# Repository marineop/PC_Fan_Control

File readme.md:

## Introduction
I have a PC fan that I removed from a CPU liquid cooler, and I'm powering it with a 12V power supply to use it for air filtration.  
However, when it's late at night, the fan's noise is a bit loud. But isn't this a PWM fan? I could use a development board to output a PWM signal and control the speed, but then I'd be short a development board.  
While searching online, I happened to come across a few useful online resources. I realized that in this day and age, this is actually possible to DIY a PCB board for simple device controls.  
* [Noctua PWM specifications white paper](https://cdn.noctua.at/media/Noctua_PWM_specifications_white_paper.pdf)
* [KiCad tutorial video from DigiKey](https://www.youtube.com/watch?v=vaCVh2SAZY4&list=PLEBQazB0HUyR24ckSZ5u05TZHV9khgA1O&index=1)
* [TI Power Dedigner](https://webench.ti.com/power-designer/)
* [OSH Park](https://oshpark.com/)
* [Mouser](https://www.mouser.com)

## Functionality

## Schematic - KiCad, Ti Power Deisgner  
* [KiCad](https://www.kicad.org/)  

## PCB Layout - KiCad  
* Front side

* Back side

### PCB Fabrication - OSH Park  

### Order Components - Mouser  

### Solder  

### Firmware  
* Programmer: STLINK-V3SET
* IDE: STM32CubeIDE
* Pin Define
    * PA7: PWM, TIM14_CH1
    * PA6: tachometer, TIM16_CH1
    * PB0: Rotary Encoder A (DI)
    * PB5: Rotary Encoder B (DI)
    * PA2: USART_TX
    * PA3: USART_RX
* Rotary Encoder Debouncing
    * Use TIM3 to periodically record last 10 pin states
        * if current state is 0, and there are at least eight 1s in the history, then change state to 1
        * if current state is 1, and there are at least eight 0s in the history, then change state to 0
* Debug USART: 115200, N, 8, 1

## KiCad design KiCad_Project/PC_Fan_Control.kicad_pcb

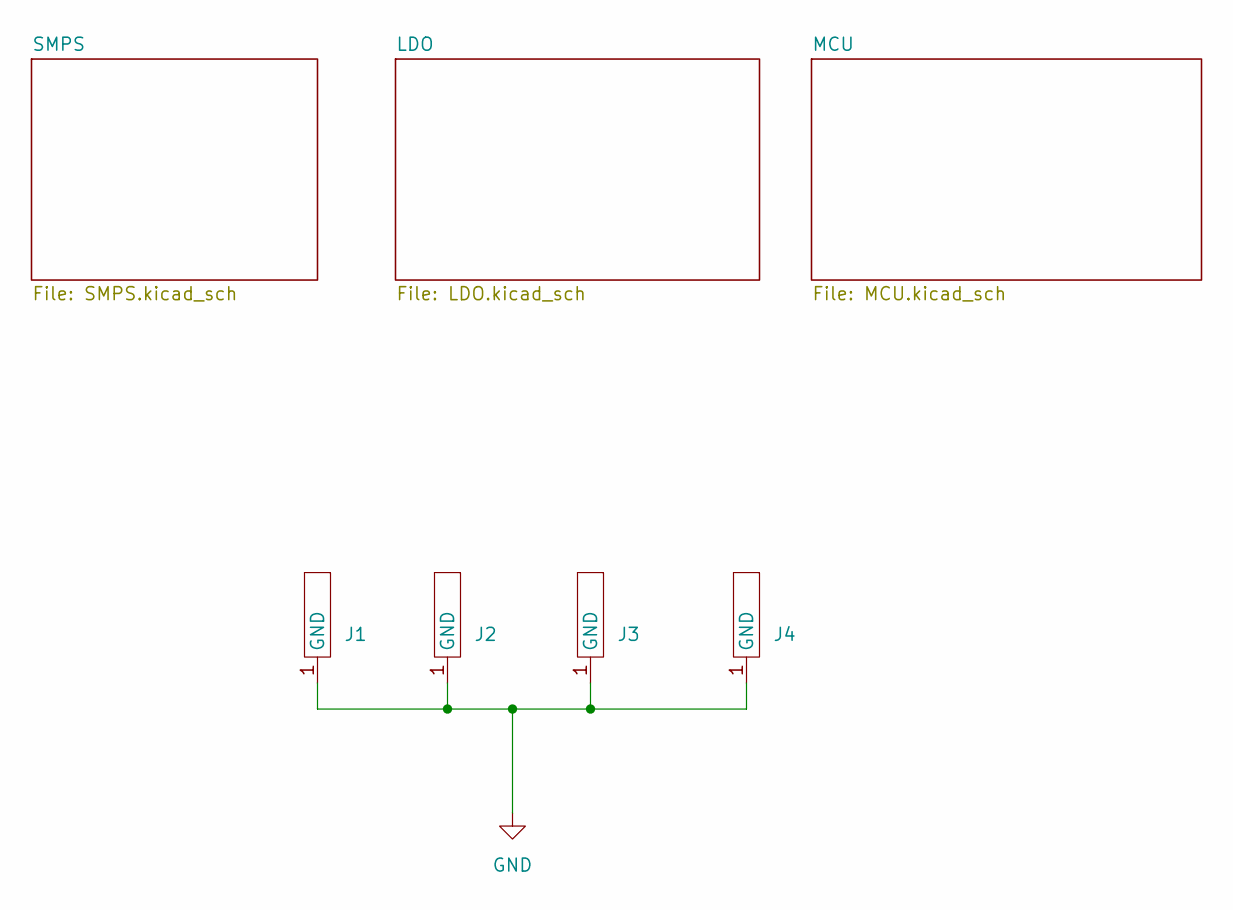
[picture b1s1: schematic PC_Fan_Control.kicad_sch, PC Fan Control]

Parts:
J1, J2, J3, J4: Standoff

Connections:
GND: J1.1 (GND), J2.1 (GND), J3.1 (GND), J4.1 (GND); also elsewhere on the board

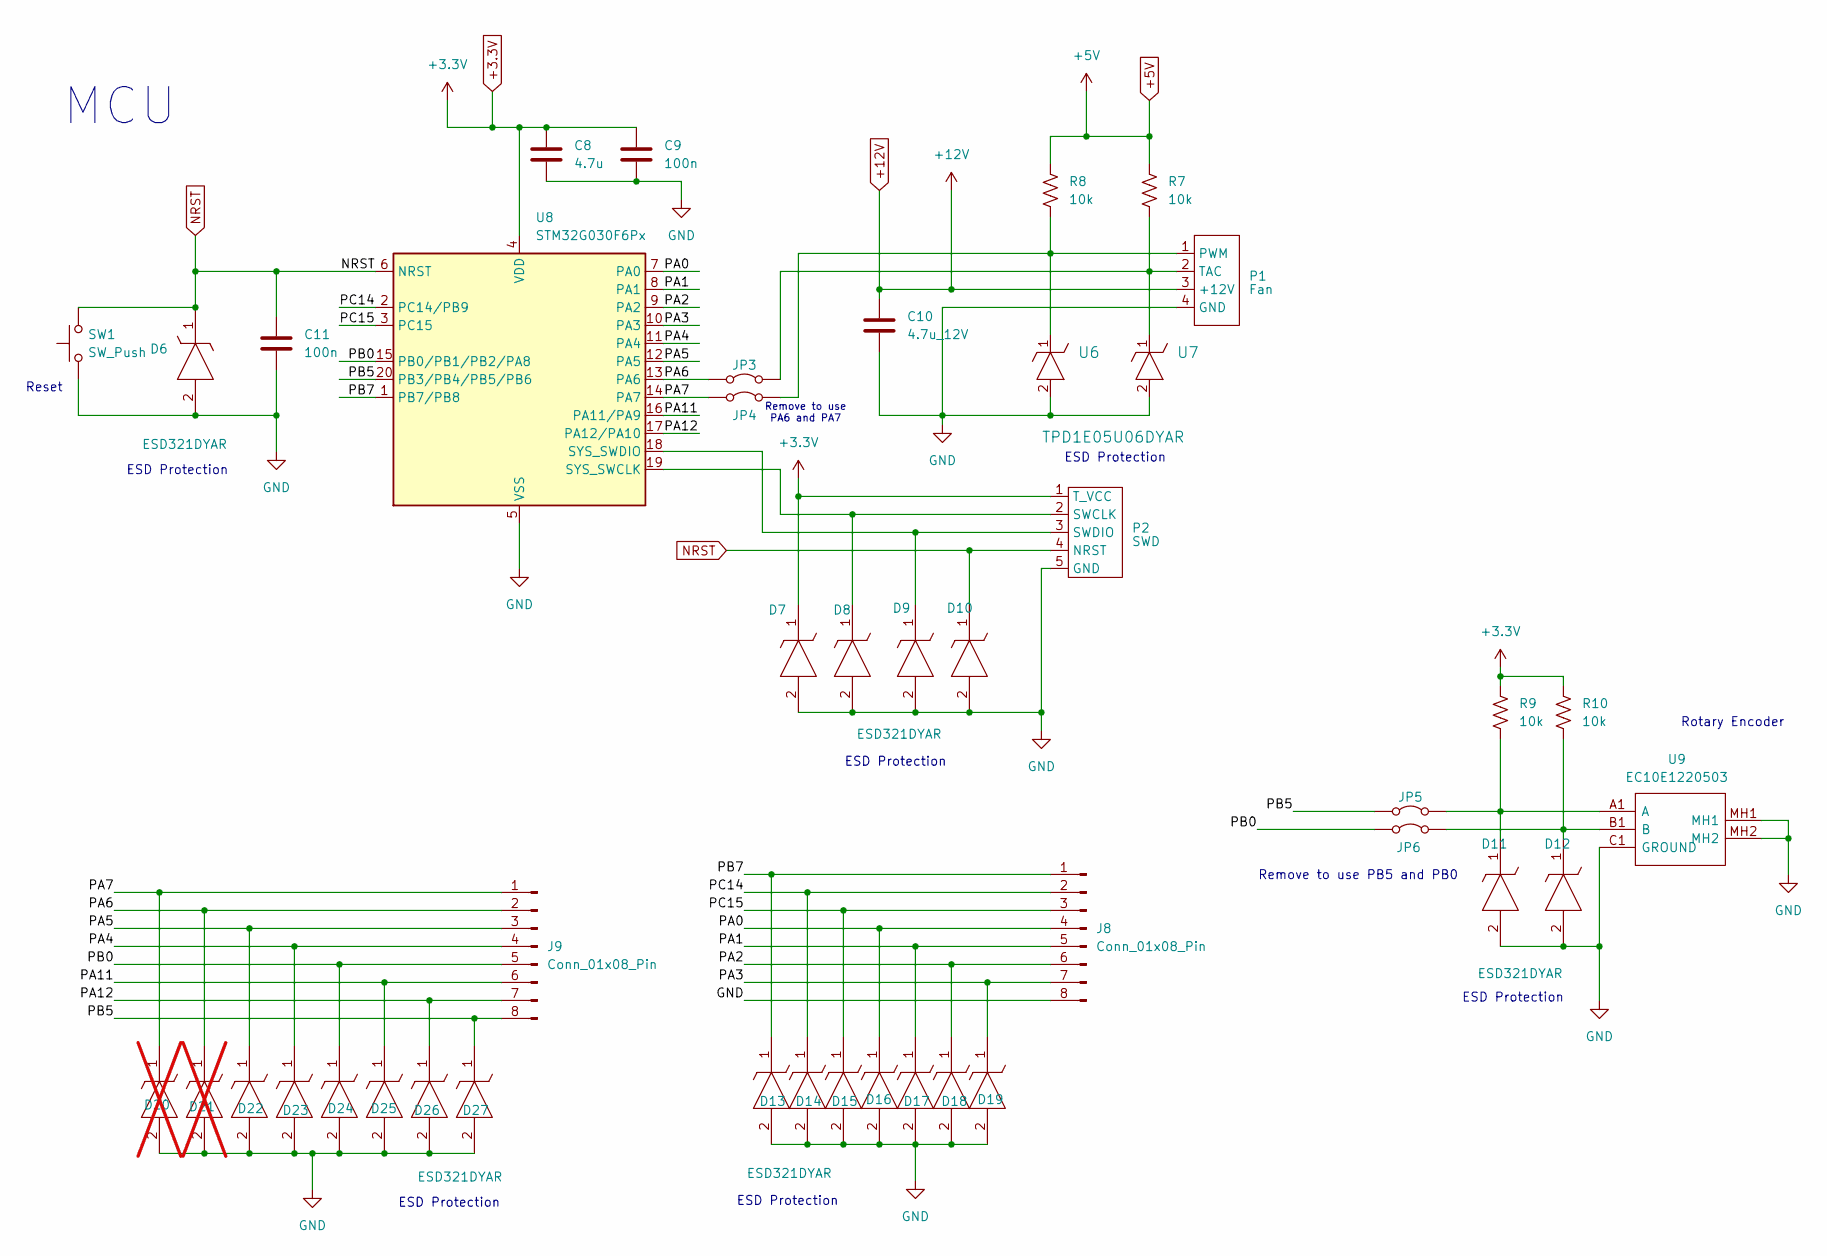
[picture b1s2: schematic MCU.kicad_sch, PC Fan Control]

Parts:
C8: 4.7u; C_0805_2012Metric_Pad1.18x1.45mm_HandSolder
C9, C11: 100n; C_0805_2012Metric_Pad1.18x1.45mm_HandSolder
C10: 4.7u_12V; C_0805_2012Metric_Pad1.18x1.45mm_HandSolder
D6, D7, D8, D9, D10, D11, D12, D13, D14, D15, D16, D17, D18, D19, D22, D23, D24, D25, D26, D27: ESD321DYAR; SOT (SOD-523)_Ti_DYA; Mouser Part Number 595-ESD321DYAR
D20, D21: ESD321DYAR; SOT (SOD-523)_Ti_DYA; Mouser Part Number 595-ESD321DYAR; not fitted
J8, J9: Conn_01x08_Pin; PinSocket_1x08_P2.54mm_Vertical
JP3, JP4, JP5, JP6: Jumper_2_Bridged; PinHeader_1x02_P2.54mm_Vertical
P1: Fan; PinHeader_1x04_P2.54mm_Horizontal
P2: SWD; PinHeader_1x05_P2.54mm_Vertical
R7, R8, R9, R10: 10k; R_0805_2012Metric_Pad1.20x1.40mm_HandSolder
SW1: SW_Push; SW_PUSH_6mm_H9.5mm
U6, U7: TPD1E05U06DYAR; SOT5x3_DYA_TEX
U8: STM32G030F6Px; TSSOP-20_4.4x6.5mm_P0.65mm
U9: EC10E1220503; Mouser Part Number 688-EC10E1220503

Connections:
+3.3V: C8.1, C9.1, D7.1, P2.1 (T_VCC), R9.1, R10.1, U8.4 (VDD); also elsewhere on the board
+5V: R7.1, R8.1; also elsewhere on the board
+12V: C10.1, P1.3 (+12V); also elsewhere on the board
/MCU/PA0: D16.1, J8.4, U8.7 (PA0)
/MCU/PA1: D17.1, J8.5, U8.8 (PA1)
/MCU/PA2: D18.1, J8.6, U8.9 (PA2)
/MCU/PA3: D19.1, J8.7, U8.10 (PA3)
/MCU/PA4: D23.1, J9.4, U8.11 (PA4)
/MCU/PA5: D22.1, J9.3, U8.12 (PA5)
/MCU/PA6: D21.1, J9.2, JP3.1 (A), U8.13 (PA6)
/MCU/PA7: D20.1, J9.1, JP4.1 (A), U8.14 (PA7)
/MCU/PA11: D25.1, J9.6, U8.16 (PA11/PA9)
/MCU/PA12: D26.1, J9.7, U8.17 (PA12/PA10)
/MCU/PB0: D24.1, J9.5, JP6.1 (A), U8.15 (PB0/PB1/PB2/PA8)
/MCU/PB5: D27.1, J9.8, JP5.1 (A), U8.20 (PB3/PB4/PB5/PB6)
/MCU/PB7: D13.1, J8.1, U8.1 (PB7/PB8)
/MCU/PC14: D14.1, J8.2, U8.2 (PC14/PB9)
/MCU/PC15: D15.1, J8.3, U8.3 (PC15)
GND: C8.2, C9.2, C10.2, C11.2, D6.2, D7.2, D8.2, D9.2, D10.2, D11.2, D12.2, D13.2, D14.2, D15.2, D16.2, D17.2, D18.2, D19.2, D20.2, D21.2, D22.2, D23.2, D24.2, D25.2, D26.2, D27.2, J8.8, P1.4 (GND), P2.5 (GND), SW1.1, U6.2, U7.2, U8.5 (VSS), U9.C1 (GROUND), U9.MH1, U9.MH2; also elsewhere on the board
NRST: C11.1, D6.1, D10.1, P2.4 (NRST), SW1.2, U8.6 (NRST)
unnamed: JP3.2 (B), P1.2 (TAC), R7.2, U7.1
unnamed: JP4.2 (B), P1.1 (PWM), R8.2, U6.1
unnamed: D11.1, JP5.2 (B), R9.2, U9.A1 (A)
unnamed: D12.1, JP6.2 (B), R10.2, U9.B1 (B)
unnamed: D8.1, P2.2 (SWCLK), U8.19 (SYS_SWCLK)
unnamed: D9.1, P2.3 (SWDIO), U8.18 (SYS_SWDIO)

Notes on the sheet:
ESD Protection
Remove to use PA6 and PA7
Rotary Encoder
MCU
Remove to use PB5 and PB0
Reset

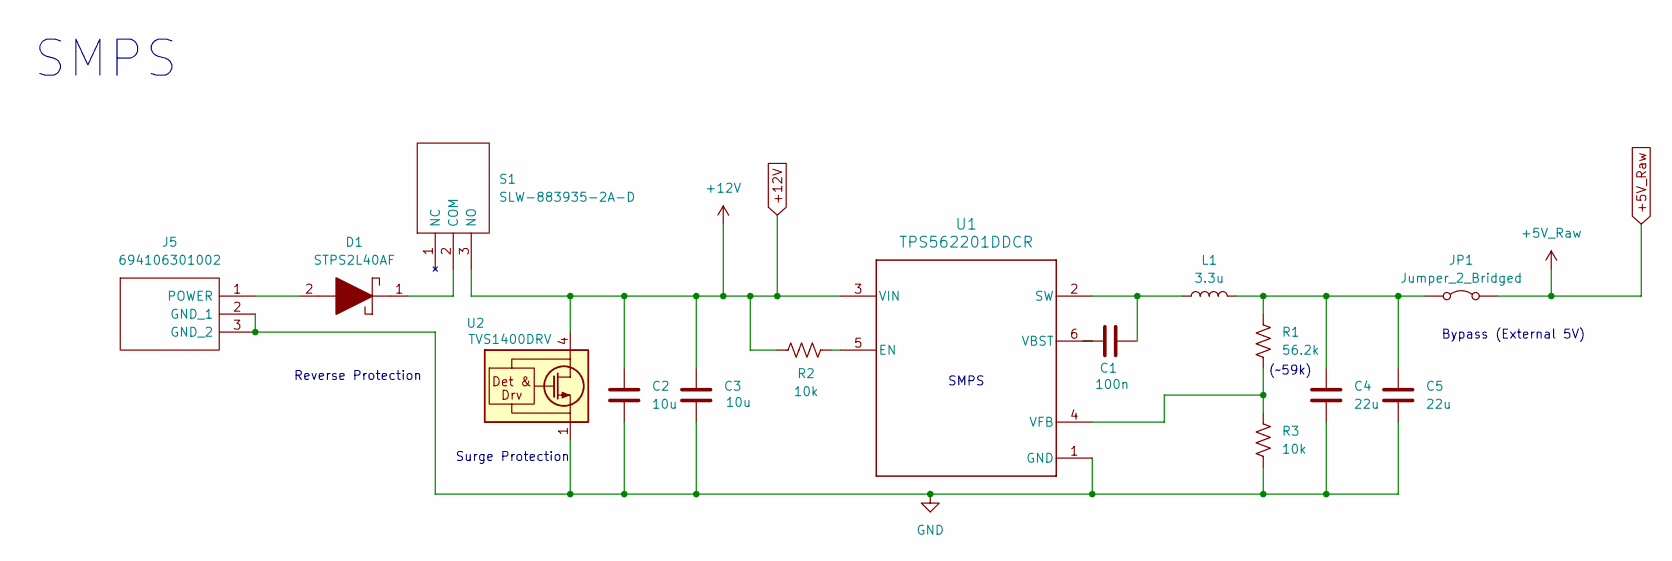
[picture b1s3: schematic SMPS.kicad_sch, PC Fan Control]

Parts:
C1: 100n; C_0603_1608Metric_Pad1.08x0.95mm_HandSolder
C2, C3: 10u; C_0805_2012Metric_Pad1.18x1.45mm_HandSolder
C4, C5: 22u; C_0603_1608Metric_Pad1.08x0.95mm_HandSolder
D1: STPS2L40AF; SODFL5226X110N; Mouser Part Number 511-STPS2L40AF
J5: 694106301002; BarrelJack_Wuerth_6941xx301002; Mouser Part Number 710-694106301002
JP1: Jumper_2_Bridged; PinHeader_1x02_P2.54mm_Vertical
L1: 3.3u; IHLP1212BZER3R3M11
R1: 56.2k; R_0805_2012Metric_Pad1.20x1.40mm_HandSolder
R2, R3: 10k; R_0805_2012Metric_Pad1.20x1.40mm_HandSolder
S1: SLW-883935-2A-D; SLW8839352AD; Mouser Part Number 179-SLW-883935-2A-D
U1: TPS562201DDCR; TSOT-23-6
U2: TVS1400DRV; WSON-6-1EP_2x2mm_P0.65mm_EP1x1.6mm

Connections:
+5V_Raw: JP1.2 (B); also elsewhere on the board
+12V: C2.1, C3.1, R2.1, S1.3 (NO), U1.3 (VIN), U2.4 (IN), U2.5 (IN), U2.6 (IN); also elsewhere on the board
GND: C2.2, C3.2, C4.2, C5.2, J5.2 (GND_1), J5.3 (GND_2), R3.2, U1.1 (GND), U2.1 (GND), U2.2 (GND), U2.3 (GND), U2.7 (GND); also elsewhere on the board
unnamed: D1.2, J5.1 (POWER)
unnamed: C4.1, C5.1, JP1.1 (A), L1.2, R1.1
unnamed: D1.1, S1.2 (COM)
unnamed: R2.2, U1.5 (EN)
unnamed: C1.2, L1.1, U1.2 (SW)
unnamed: C1.1, U1.6 (VBST)
unnamed: R1.2, R3.1, U1.4 (VFB)

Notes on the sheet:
Surge Protection
Reverse Protection
SMPS
Bypass (External 5V)
(~59k)

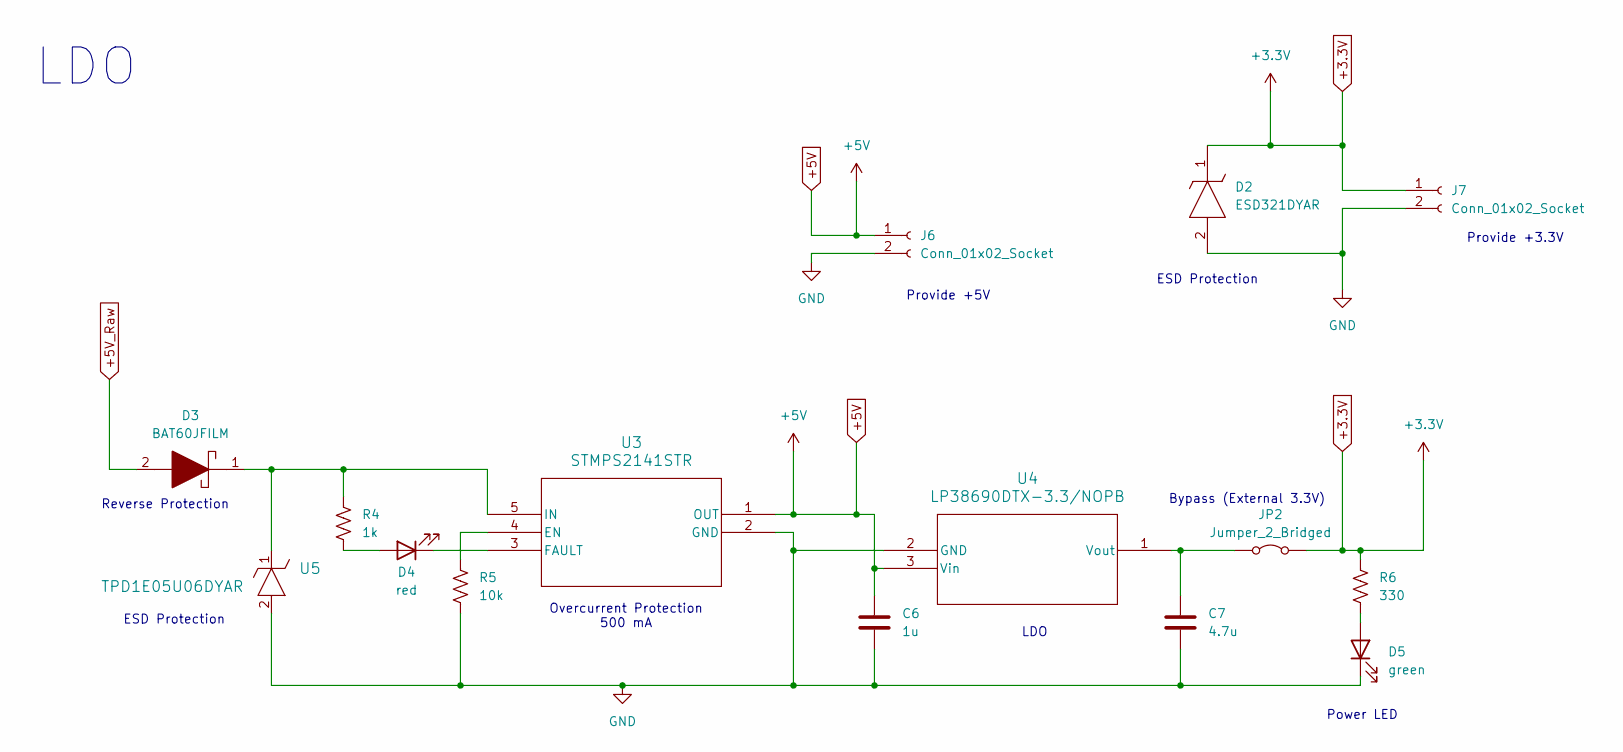
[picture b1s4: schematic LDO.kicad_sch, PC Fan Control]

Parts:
C6: 1u; C_0402_1005Metric_Pad0.74x0.62mm_HandSolder
C7: 4.7u; C_0402_1005Metric_Pad0.74x0.62mm_HandSolder
D2: ESD321DYAR; SOT (SOD-523)_Ti_DYA; Mouser Part Number 595-ESD321DYAR
D3: BAT60JFILM; SOD2513X117N; Mouser Part Number 511-BAT60JFILM
D4: red; LED_D3.0mm
D5: green; LED_D3.0mm
J6, J7: Conn_01x02_Socket; PinSocket_1x02_P2.54mm_Vertical
JP2: Jumper_2_Bridged; PinHeader_1x02_P2.54mm_Vertical
R4: 1k; R_0805_2012Metric_Pad1.20x1.40mm_HandSolder
R5: 10k; R_0805_2012Metric_Pad1.20x1.40mm_HandSolder
R6: 330; R_0805_2012Metric_Pad1.20x1.40mm_HandSolder
U3: STMPS2141STR; SOT23-5L_STM
U4: LP38690DTX-3.3/NOPB; TO252-3
U5: TPD1E05U06DYAR; SOT5x3_DYA_TEX

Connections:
+3.3V: D2.1, J7.1, JP2.2 (B), R6.1; also elsewhere on the board
+5V: C6.1, J6.1, U3.1 (OUT), U4.3 (Vin); also elsewhere on the board
+5V_Raw: D3.2; also elsewhere on the board
GND: C6.2, C7.2, D2.2, D5.1 (K), J6.2, J7.2, R5.2, U3.2 (GND), U4.2 (GND), U5.2; also elsewhere on the board
unnamed: D4.2 (A), R4.2
unnamed: D4.1 (K), U3.3 (FAULT)
unnamed: D5.2 (A), R6.2
unnamed: C7.1, JP2.1 (A), U4.1 (Vout)
unnamed: R5.1, U3.4 (EN)
unnamed: D3.1, R4.1, U3.5 (IN), U5.1

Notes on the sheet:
Power LED
Overcurrent Protection 500 mA
ESD Protection
Reverse Protection
Provide +5V
Provide +3.3V
Bypass (External 3.3V)
LDO

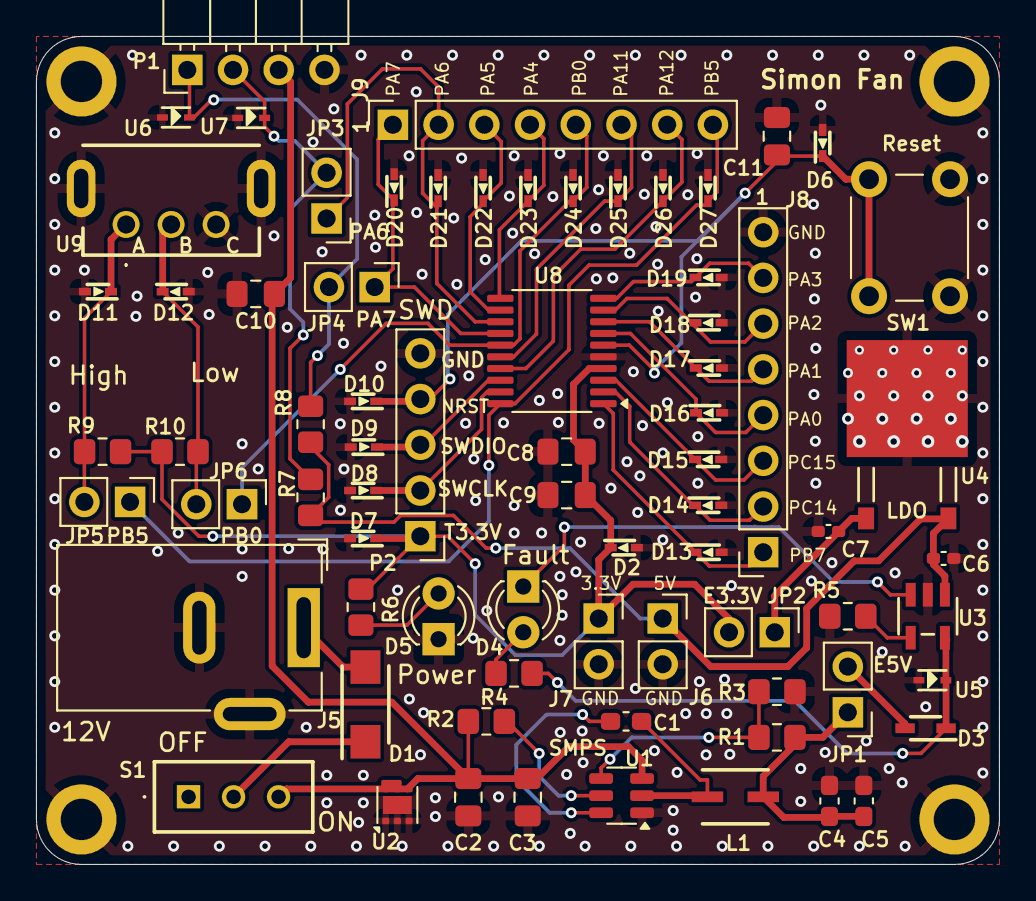
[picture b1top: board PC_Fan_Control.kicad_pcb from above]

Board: 2 copper layers, 53.5 x 46.0 mm, 77 parts (0 on the bottom side), 40 nets.

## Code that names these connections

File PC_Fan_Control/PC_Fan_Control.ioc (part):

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Mcu.Name=STM32G030F6Px
Mcu.Package=TSSOP20
Mcu.UserName=STM32G030F6Px
PA13.Mode=Serial_Wire
PA13.Signal=SYS_SWDIO
PA14-BOOT0.Mode=Serial_Wire
PA14-BOOT0.Signal=SYS_SWCLK
PA14-BOOT0__PA15.StandardMode=true
PA2.Mode=Asynchronous
PA2.Signal=USART2_TX
PA3.Mode=Asynchronous
PA3.Signal=USART2_RX
PA6.GPIOParameters=GPIO_ModeDefaultPP,GPIO_Label
PA6.GPIO_Label=TIM16_CH1_TAC
PA6.GPIO_ModeDefaultPP=GPIO_MODE_AF_OD
PA6.Signal=S_TIM16_CH1
PA7.GPIOParameters=GPIO_ModeDefaultPP,GPIO_Label
PA7.GPIO_Label=PWM
PA7.GPIO_ModeDefaultPP=GPIO_MODE_AF_OD
PA7.Signal=S_TIM14_CH1
PB0.GPIOParameters=GPIO_Label
PB0.GPIO_Label=Encoder
PB0.Signal=S_TIM3_CH3
PB0__PB1__PB2__PA8.StandardMode=true
PB3__PB4__PB5__PB6.StandardMode=true
PB5.GPIOParameters=GPIO_ModeDefaultPP,GPIO_Label
PB5.GPIO_Label=Encoder
PB5.GPIO_ModeDefaultPP=GPIO_MODE_AF_PP
PB5.Signal=S_TIM3_CH2
PB7__PB8.StandardMode=true
PC14-OSC32_IN\ (PC14)__PB9.StandardMode=true
RCC.HSE_VALUE=8000000
RCC.SYSCLKFreq_VALUE=50000000
RCC.SYSCLKSource=RCC_SYSCLKSOURCE_PLLCLK
board=custom

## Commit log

2025-11-07 Create project
2025-11-07 Fix MD image

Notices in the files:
KiCad_Project/PC_Fan_Control.kicad_pcb:
License: MIT
